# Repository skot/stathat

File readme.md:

## StatHat

A RPi Hat interface to a 24VAC thermostat.

### Thermostat Pins

| Thermostat pin name | Pin symbol | RPi GPIO |
| --- | --- | --- |
| COOL | `Y` | `GPIO17` (physical pin 11) |
| HEAT | `W` | `GPIO16` (physical pin 36) |
| FAN | `G` | `GPIO18` (physical pin 12) |
| HEAT2 | `W2` | `GPIO19` (physical pin 35) |
| COMMON | `C` | N/A |

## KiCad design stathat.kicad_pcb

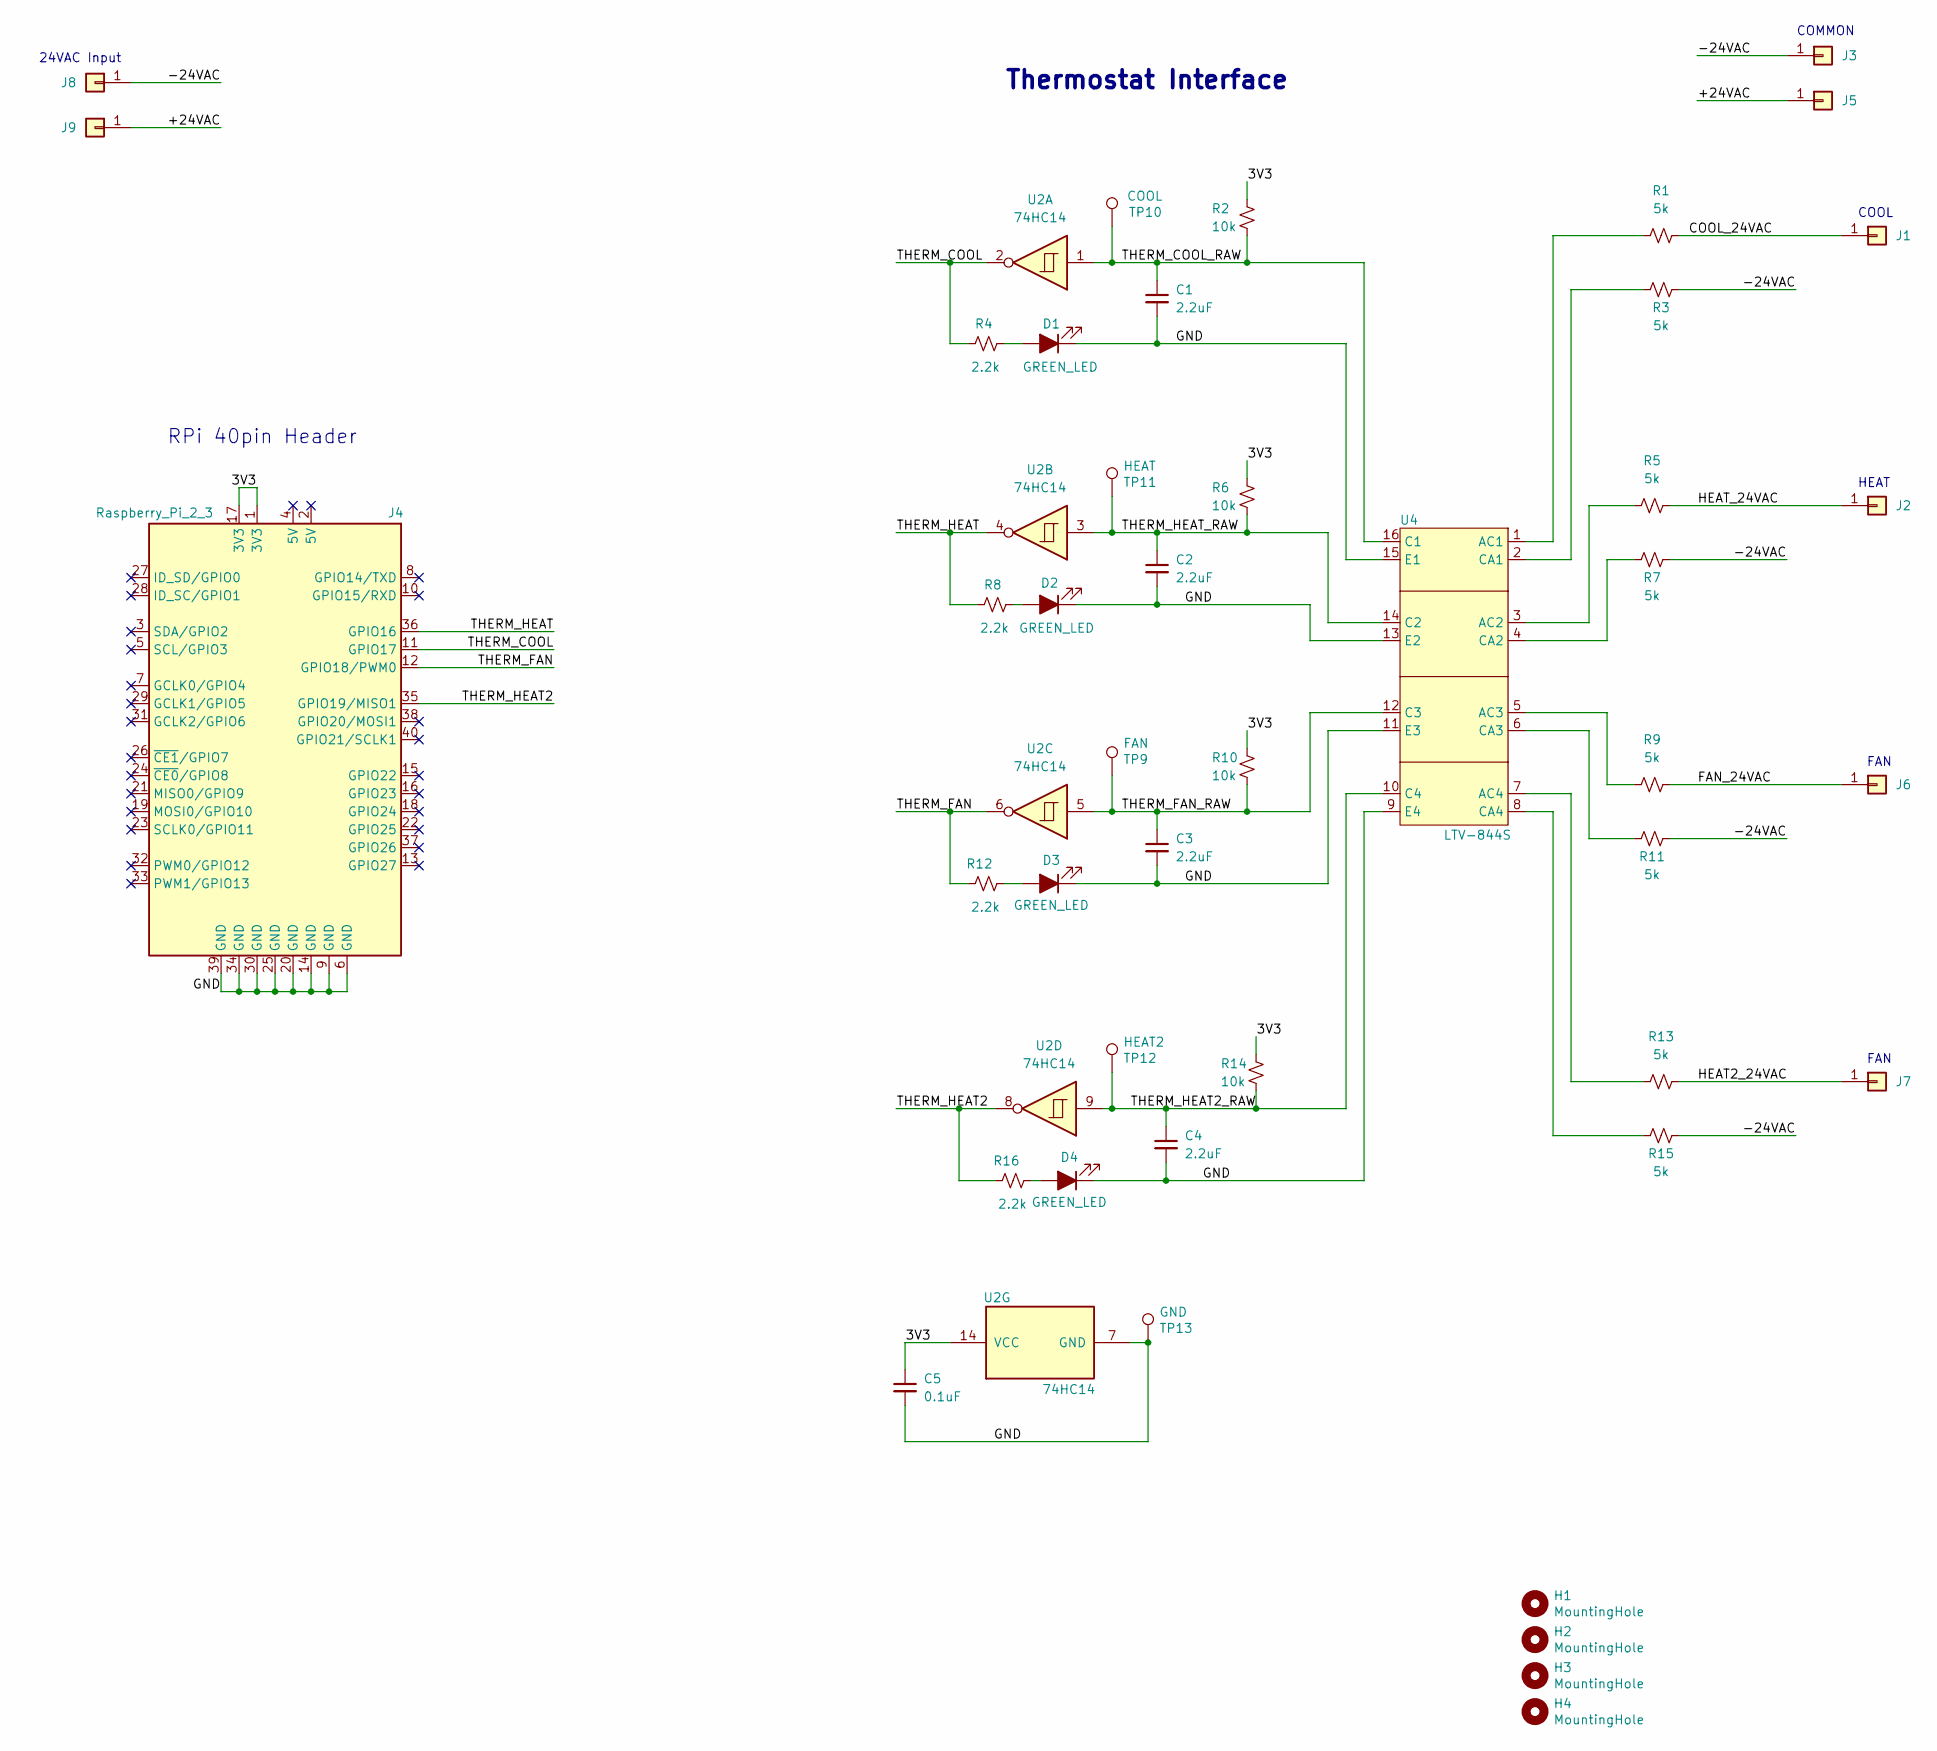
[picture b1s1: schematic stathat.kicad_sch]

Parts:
C1, C2, C3, C4: 2.2uF; C_0402_1005Metric; PARTNO CL10A225KO8NNNC
C5: 0.1uF; C_0402_1005Metric; PARTNO CL05B104KP5NNNC
D1, D2, D3, D4: GREEN_LED; LED_0402_1005Metric; PARTNO 150040VS73240
H1, H2, H3, H4: MountingHole; MountingHole_2.7mm_M2.5
J1, J2, J3, J5, J6, J7, J8, J9: Conn_01x01; 63862-1; PARTNO 63862-1
J4: Raspberry_Pi_2_3; ESQ-120-14-T-D; PARTNO PPPC202LFBN-RC; LCSC C2977589
R1, R3, R5, R7, R9, R11, R13, R15: 5k; R_1210_3225Metric; PARTNO RC1210FR-075K1L
R2, R6, R10, R14: 10k; R_0402_1005Metric; PARTNO RMCF0402FT10K0
R4, R8, R12, R16: 2.2k; R_0402_1005Metric; PARTNO RC0402FR-072K2L
TP9: FAN; TestPoint_Pad_D1.0mm
TP10: COOL; TestPoint_Pad_D1.0mm
TP11: HEAT; TestPoint_Pad_D1.0mm
TP12: HEAT2; TestPoint_Pad_D1.0mm
TP13: GND; TestPoint_Pad_D1.0mm
U2: 74HC14; SOIC-14_3.9x8.7mm_P1.27mm; PARTNO SN74HC14DR
U4: LTV-844S; OPTO-SMD-16_L19.8-W6.5-P2.54-LS10.2-BL; LCSC Part C575506

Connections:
/3V3: C5.1, J4.1 (3V3), J4.17 (3V3), R2.2, R6.2, R10.2, R14.2, U2.14 (VCC)
/+24VAC: J5.1 (Pin_1_1), J9.1 (Pin_1_1)
/-24VAC: J3.1 (Pin_1_1), J8.1 (Pin_1_1), R3.2, R7.1, R11.1, R15.1
/COOL_24VAC: J1.1 (Pin_1_1), R1.1
/FAN_24VAC: J6.1 (Pin_1_1), R9.1
/GND: C1.2, C2.2, C3.2, C4.2, C5.2, D1.1 (K), D2.1 (K), D3.1 (K), D4.1 (K), J4.6 (GND), J4.9 (GND), J4.14 (GND), J4.20 (GND), J4.25 (GND), J4.30 (GND), J4.34 (GND), J4.39 (GND), TP13.1 (1_1), U2.7 (GND), U4.9 (E4), U4.11 (E3), U4.13 (E2), U4.15 (E1)
/HEAT2_24VAC: J7.1 (Pin_1_1), R13.1
/HEAT_24VAC: J2.1 (Pin_1_1), R5.1
/THERM_COOL: J4.11 (GPIO17), R4.2, U2.2
/THERM_COOL_RAW: C1.1, R2.1, TP10.1 (1_1), U2.1, U4.16 (C1)
/THERM_FAN: J4.12 (GPIO18/PWM0), R12.2, U2.6
/THERM_FAN_RAW: C3.1, R10.1, TP9.1 (1_1), U2.5, U4.12 (C3)
/THERM_HEAT: J4.36 (GPIO16), R8.2, U2.4
/THERM_HEAT2: J4.35 (GPIO19/MISO1), R16.2, U2.8
/THERM_HEAT2_RAW: C4.1, R14.1, TP12.1 (1_1), U2.9, U4.10 (C4)
/THERM_HEAT_RAW: C2.1, R6.1, TP11.1 (1_1), U2.3, U4.14 (C2)
unnamed: D1.2 (A), R4.1
unnamed: D2.2 (A), R8.1
unnamed: D3.2 (A), R12.1
unnamed: D4.2 (A), R16.1
unnamed: R1.2, U4.1 (AC1)
unnamed: R5.2, U4.3 (AC2)
unnamed: R9.2, U4.5 (AC3)
unnamed: R13.2, U4.7 (AC4)
unnamed: R3.1, U4.2 (CA1)
unnamed: R7.2, U4.4 (CA2)
unnamed: R11.2, U4.6 (CA3)
unnamed: R15.2, U4.8 (CA4)

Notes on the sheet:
Thermostat Interface
RPi 40pin Header
COMMON
HEAT
COOL
FAN
24VAC Input

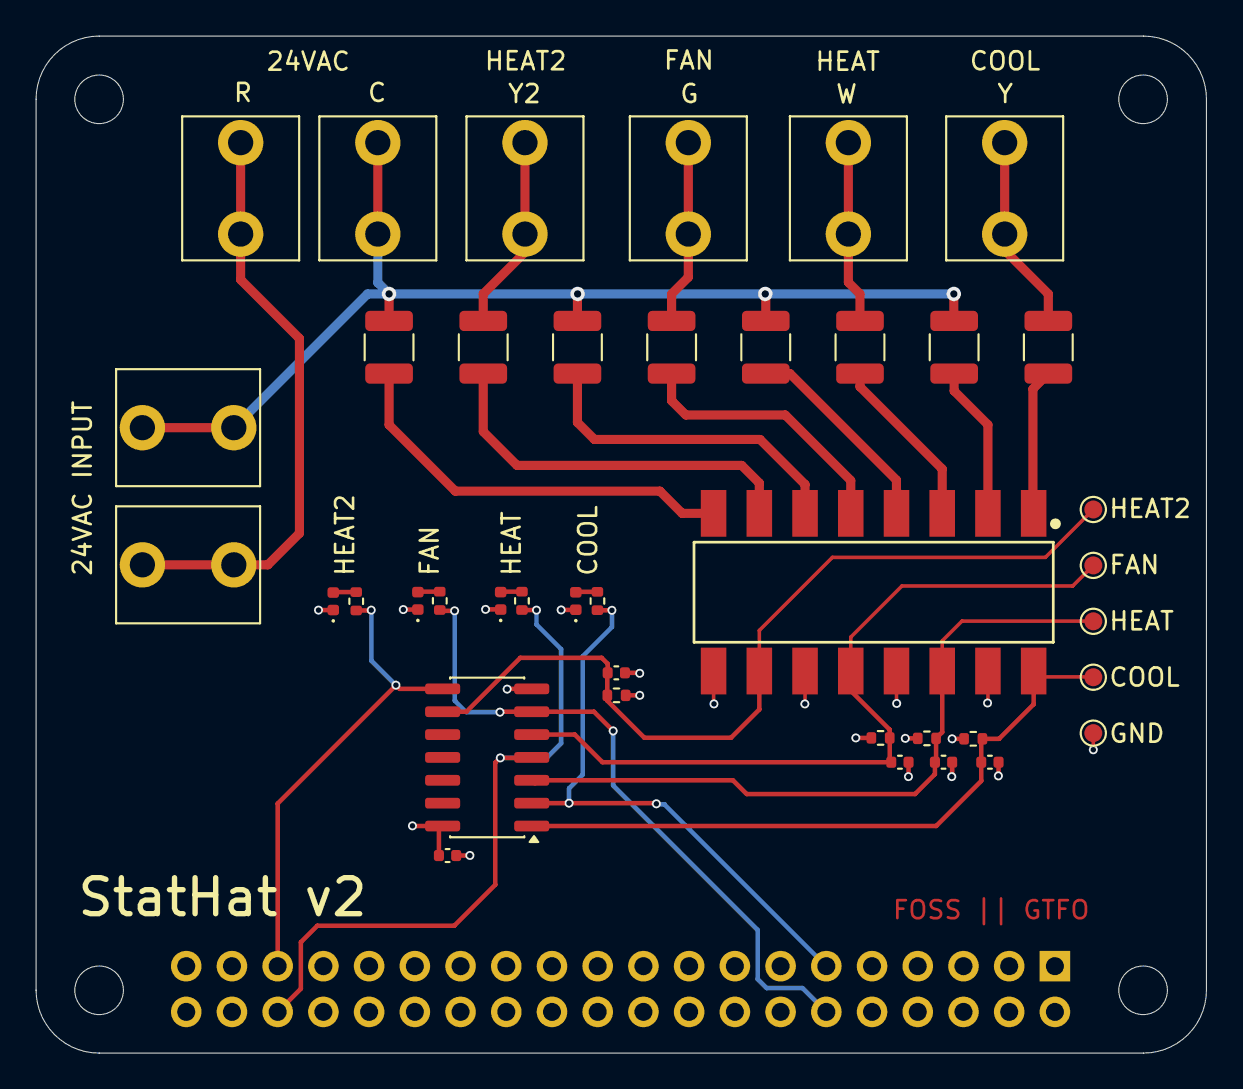
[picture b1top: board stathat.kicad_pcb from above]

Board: 4 copper layers, 65.0 x 56.5 mm, 45 parts (0 on the bottom side), 28 nets.

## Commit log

2026-04-23 initial import
2026-04-24 fixed schematic. added part numbers. routed PCB
2026-04-24 added render, updated readme
2026-04-24 minor DRC and ERC cleanup. updated render
2026-04-24 add license
2026-05-07 add fix for #1. move all vias out of pads. clean up traces. bump version number
2026-05-08 updated render for v2
